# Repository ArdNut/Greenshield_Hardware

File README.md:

# Greenshield Hardware

This repository contains the design artifacts for the circuit and PCB layout
of the Greenshield Arduino shield created for chapter 10 of "Arduino: A Technical Reference".

These were creating using CadSoft's Eagle design tool version 6.5.0 for Linux.

Copyight 2015-2016 John M. Hughes

O'Reilly appreciates, but does not require, attribution. An attribution usually
includes the title, author, publisher, and ISBN. For example:

Arduino: A Technical Reference, by John M. Hughes. Copyright 2016 O’Reilly
Media, Inc., ISBN: 978-1-4919-2176-0.

If you feel your use of code examples falls outside fair use or the permission
given above, feel free to contact permissions@oreilly.com.

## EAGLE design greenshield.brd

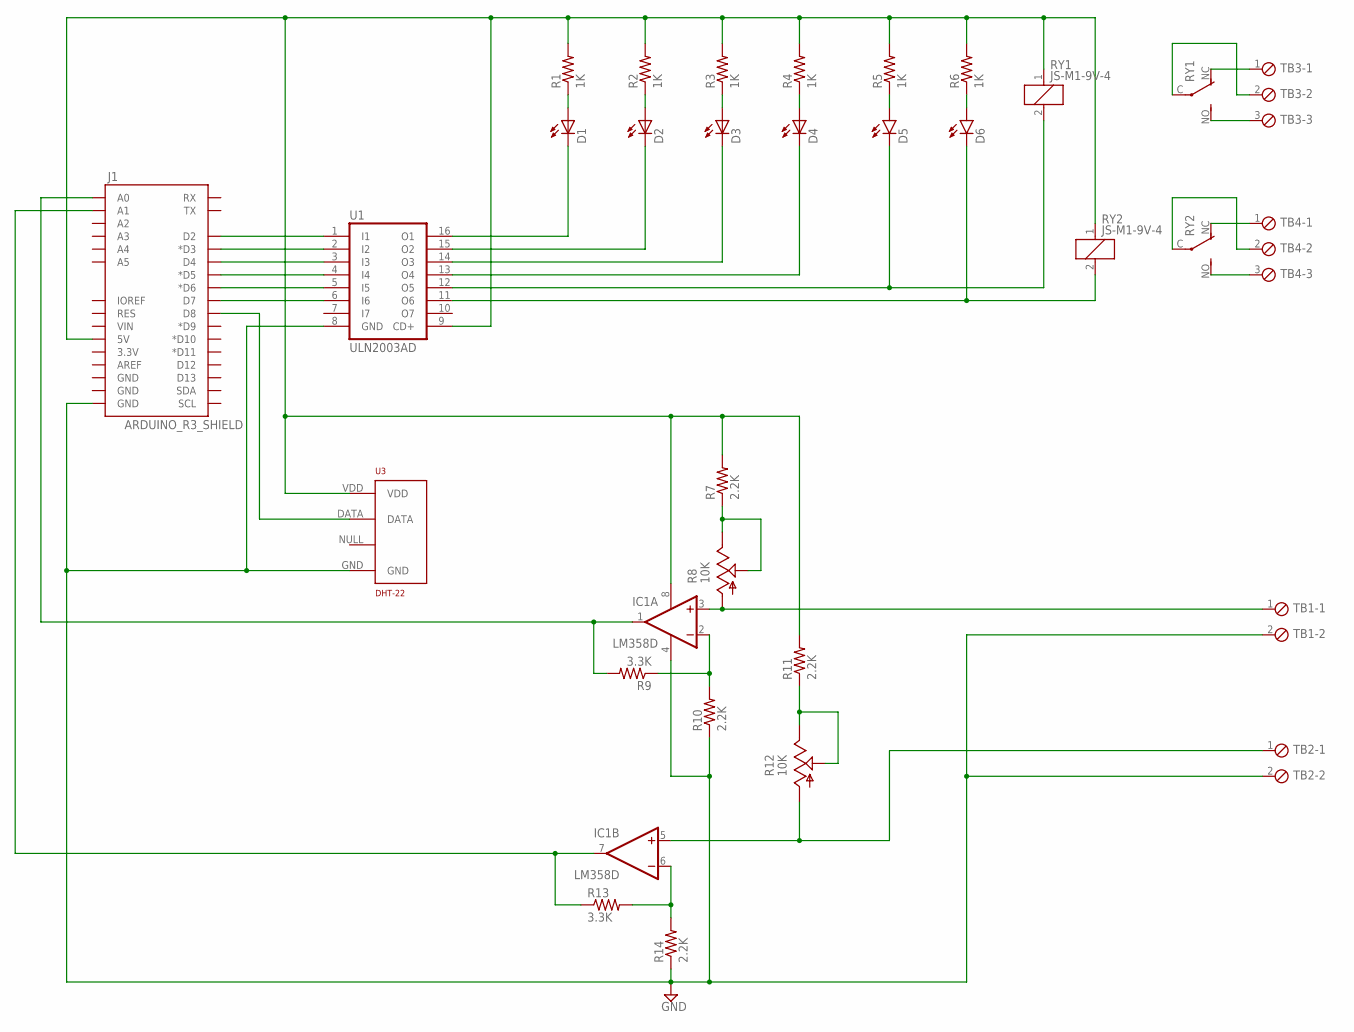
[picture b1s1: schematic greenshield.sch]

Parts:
D1, D2, D3, D4, D5, D6: LED3MM
IC1: LM358D; SO08
J1: ARDUINO_R3_SHIELD; UNO_R3_SHIELD
R1, R2, R3, R4, R5, R6: 1K; 0805
R7, R10, R11, R14: 2.2K; 0805
R8, R12: 10K; S64W
R9, R13: 3.3K; 0805
RY1, RY2: JS-M1-9V-4; JS-M
TB1, TB2: MPT2; 2POL254
TB3, TB4: MPT3; 3POL254
U1: ULN2003AD; SO16
U3: DHT-22; RHT03_DHT-22

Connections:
GND: IC1.4 (V-), J1.GND@0 (GND), R10.1, R14.1, TB1.2, TB2.2, U1.8 (GND), U3.GND
unnamed: J1.D2, U1.1 (I1)
unnamed: J1.D3 (*D3), U1.2 (I2)
unnamed: J1.D4, U1.3 (I3)
unnamed: D6.K (C), RY2.2, U1.11 (O6)
unnamed: J1.D5 (*D5), U1.4 (I4)
unnamed: J1.D6 (*D6), U1.5 (I5)
unnamed: J1.D7, U1.6 (I6)
unnamed: D5.K (C), RY1.2, U1.12 (O5)
unnamed: RY1.NC (O), TB3.1
unnamed: D1.K (C), U1.16 (O1)
unnamed: D6.A, R6.1
unnamed: D2.K (C), U1.15 (O2)
unnamed: D3.K (C), U1.14 (O3)
unnamed: D4.K (C), U1.13 (O4)
unnamed: D5.A, R5.1
unnamed: RY1.NO (S), TB3.3
unnamed: D1.A, R1.1
unnamed: D2.A, R2.1
unnamed: D3.A, R3.1
unnamed: D4.A, R4.1
unnamed: RY2.NC (O), TB4.1
unnamed: RY2.NO (S), TB4.3
unnamed: RY2.C, TB4.2
unnamed: RY1.C, TB3.2
unnamed: IC1.8 (V+), J1.5V, R1.2, R2.2, R3.2, R4.2, R5.2, R6.2, R7.2, R11.2, RY1.1, RY2.1, U1.9 (CD+), U3.VDD
unnamed: R7.1, R8.E, R8.S
unnamed: R11.1, R12.E, R12.S
unnamed: IC1.5 (+IN), R12.A, TB2.1
unnamed: IC1.6 (-IN), R13.2, R14.2
unnamed: IC1.7 (OUT), J1.A1, R13.1
unnamed: J1.D8, U3.DATA
unnamed: IC1.2 (-IN), R9.1, R10.2
unnamed: IC1.1 (OUT), J1.A0, R9.2
unnamed: IC1.3 (+IN), R8.A, TB1.1

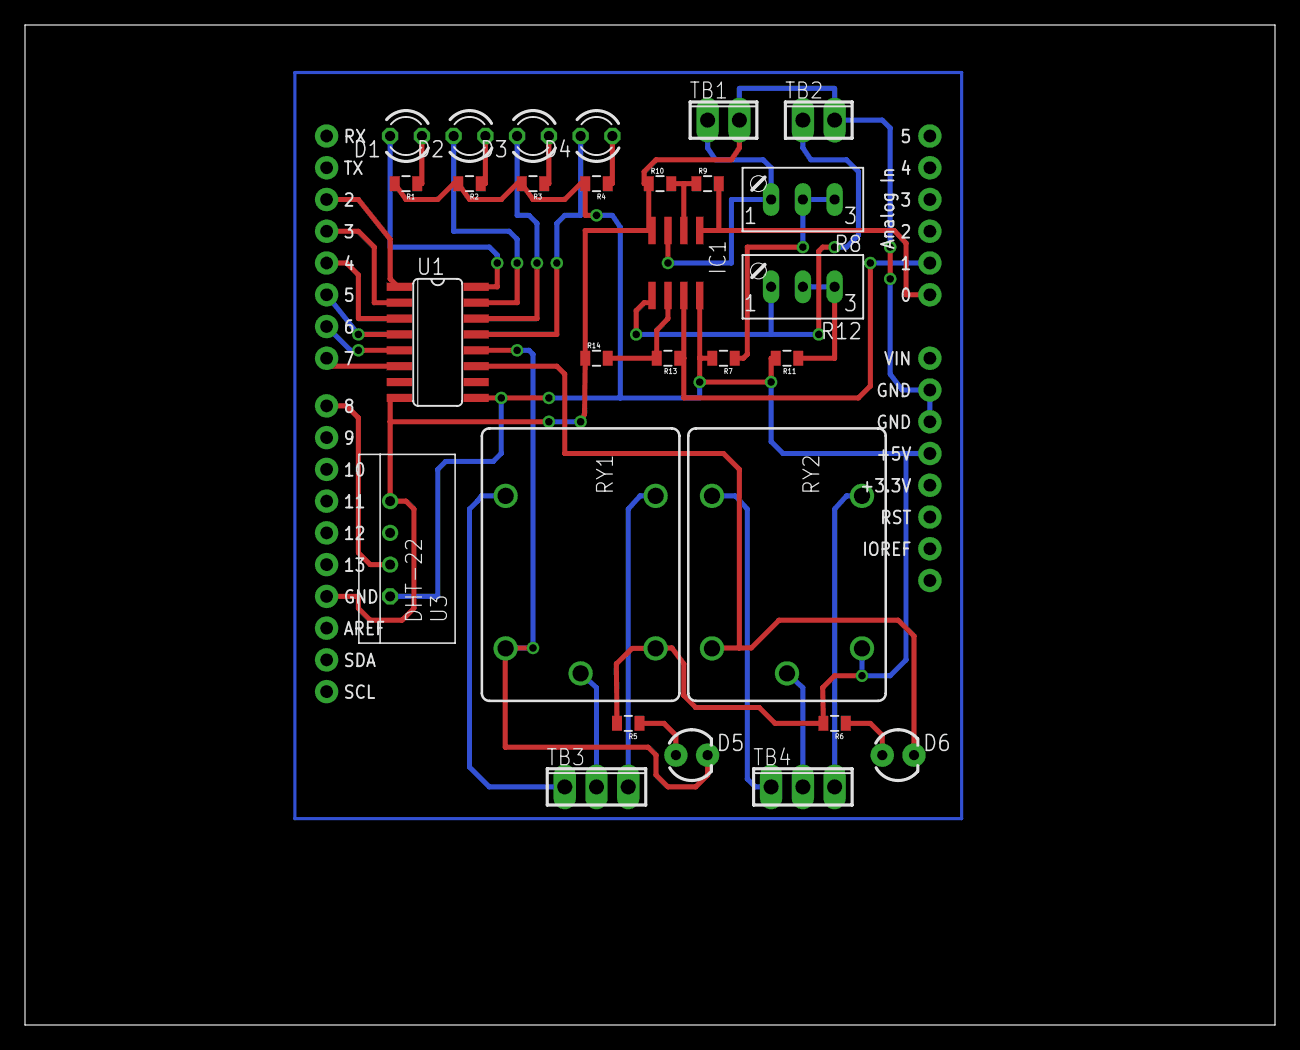
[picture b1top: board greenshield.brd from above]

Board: 2 copper layers, 100.0 x 80.0 mm, 30 parts (0 on the bottom side), 35 nets.

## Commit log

2016-02-18 Revised to include source and usage information.
2016-02-18 Tweaked the text to improve the formatting
2016-05-14 Added list of files to README.md
2016-05-14 Removed PCB file manifest (these aren't version controlled items)
2016-07-08 Revised readme

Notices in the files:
parts and their libraries:
SparkFun-LED: Licensing: Creative Commons ShareAlike 4.0 International - https://creativecommons.org/licenses/by-sa/4.0
